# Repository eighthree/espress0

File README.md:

# espress0 prototype board
A Trinket m0 with SPI Flash + charge circuit 

# build one
https://oshpark.com

# license
Open Source
Creative Commons Attribution, Share-Alike license, check license.txt for more information. Derivative of "Trinket M0" (https://www.adafruit.com/product/3500)

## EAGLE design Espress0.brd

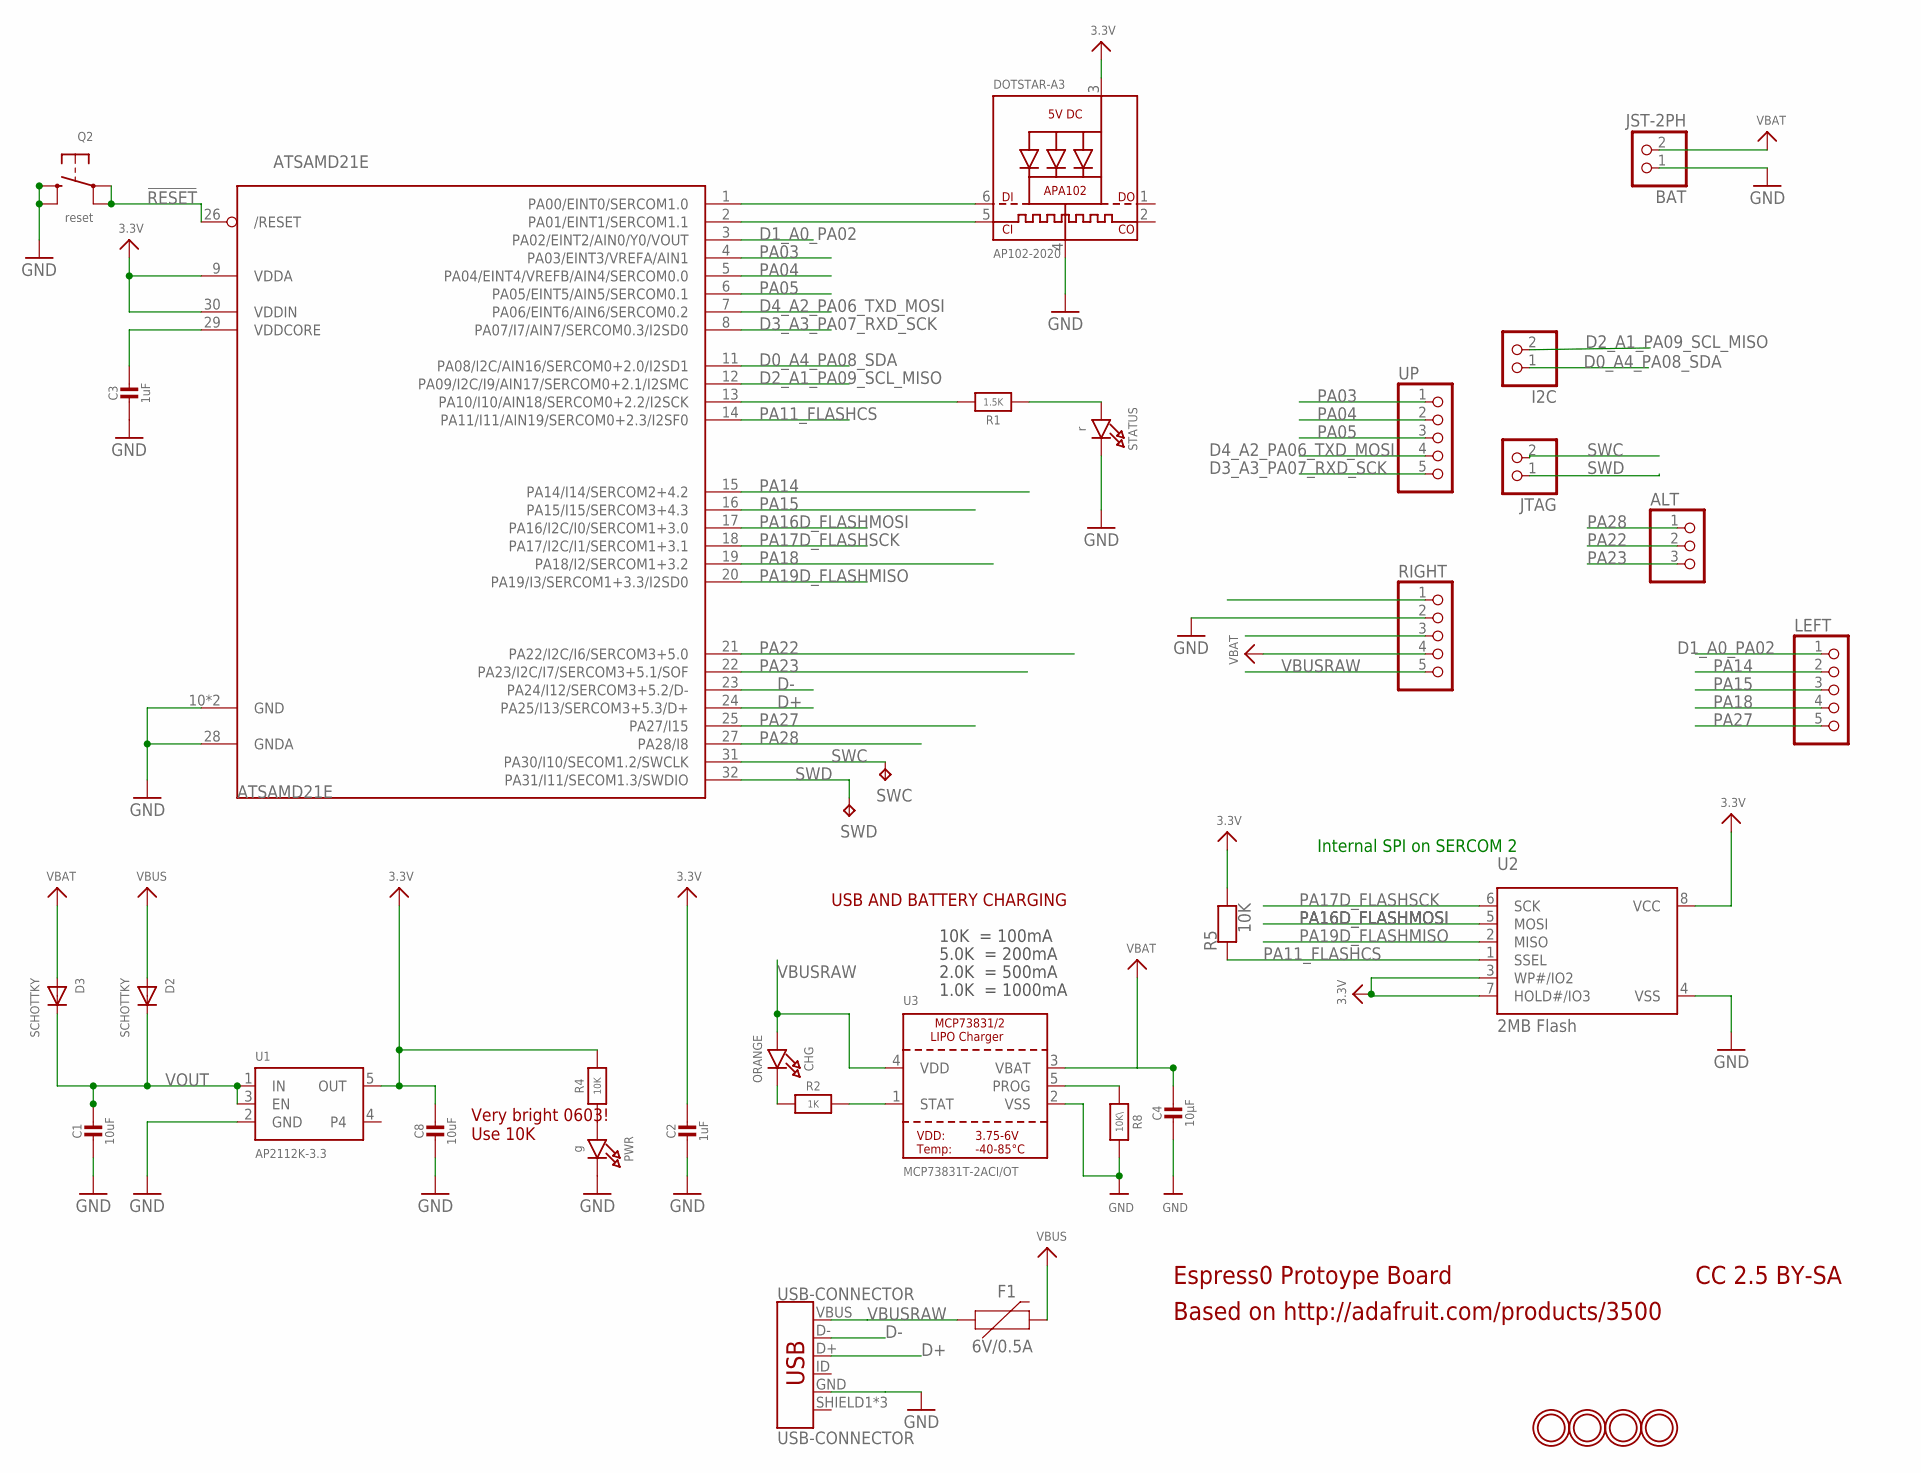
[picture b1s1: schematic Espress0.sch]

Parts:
ALT: PINHD-1X3CB; 1X03-CLEANBIG
ATSAMD21E: ATSAMD21E; QFN32_5MM
BAT: JST-2PH; JSTPH2
C1, C8: 10uF; 0805-NO
C2, C3: 1uF; 0603-NO
C4: 10µF; 0805-NO
CHG: ORANGE; CHIPLED_0805_NOOUTLINE
D2, D3: SCHOTTKY; SOD-123FL
DOTSTAR-A3: AP102-2020; APA102_2020
F1: 6V/0.5A; 1206
I2C: HEADER-1X2ROUND; 1X02_ROUND
JTAG: HEADER-1X2ROUND; 1X02_ROUND
LEFT: HEADER-1X576MIL; 1X05_ROUND_76
PWR: g; CHIPLED_0603_NOOUTLINE
Q2: reset; BTN_KMR2_4.6X2.8
R1: 1.5K; 0603-NO
R2: 1K; 0603-NO
R4, R5: 10K; 0603-NO
R8: 10K\; 0603-NO
RIGHT: HEADER-1X576MIL; 1X05_ROUND_76
STATUS: r; CHIPLED_0603_NOOUTLINE
SWC: TPB1,27; B1,27
SWD: TPB1,27; B1,27
U1: AP2112K-3.3; SOT23-5
U2: 2MB Flash; SOIC8_208MIL
U3: MCP73831T-2ACI/OT; SOT23-5
U$8, U$9, U$13, U$14: MOUNTINGHOLE2.0; MOUNTINGHOLE_2.0_PLATED
UP: HEADER-1X576MIL; 1X05_ROUND_76
USB-CONNECTOR: USB-CONNECTOR; USB-B-MICRO-SMD

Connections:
3.3V: ATSAMD21E.9 (VDDA), ATSAMD21E.30 (VDDIN), C2.1, C8.1, DOTSTAR-A3.3 (VDD), R4.2, R5.2, RIGHT.3, U1.5 (OUT), U2.3 (WP#/IO2), U2.7 (HOLD#/IO3), U2.8 (VCC)
!RESET: ATSAMD21E.26 (/RESET), Q2.A, Q2.A' (P1), RIGHT.1
A3: ATSAMD21E.1 (PA00/EINT0/SERCOM1.0), DOTSTAR-A3.6 (DI)
D0_A4_PA08_SDA: ATSAMD21E.11 (PA08/I2C/AIN16/SERCOM0+2.0/I2SD1), I2C.1
D1_A0_PA02: ATSAMD21E.3 (PA02/EINT2/AIN0/Y0/VOUT), LEFT.1
D2_A1_PA09_SCL_MISO: ATSAMD21E.12 (PA09/I2C/I9/AIN17/SERCOM0+2.1/I2SMC), I2C.2
D3_A3_PA07_RXD_SCK: ATSAMD21E.8 (PA07/I7/AIN7/SERCOM0.3/I2SD0), UP.5
D4_A2_PA06_TXD_MOSI: ATSAMD21E.7 (PA06/EINT6/AIN6/SERCOM0.2), UP.4
D+: ATSAMD21E.24 (PA25/I13/SERCOM3+5.3/D+), USB-CONNECTOR.D+
D-: ATSAMD21E.23 (PA24/I12/SERCOM3+5.2/D-), USB-CONNECTOR.D-
GND: ATSAMD21E.10 (GND), ATSAMD21E.28 (GNDA), ATSAMD21E.33 (GND), BAT.1, C1.2, C2.2, C3.2, C4.2, C8.2, DOTSTAR-A3.4 (GND), PWR.C, Q2.B (S), Q2.B' (S1), R8.2, RIGHT.2, STATUS.C, U1.2 (GND), U2.4 (VSS), U3.2 (VSS), USB-CONNECTOR.GND
unnamed: R1.1, STATUS.A
unnamed: ATSAMD21E.13 (PA10/I10/AIN18/SERCOM0+2.2/I2SCK), R1.2
unnamed: PWR.A, R4.1
unnamed: ATSAMD21E.2 (PA01/EINT1/SERCOM1.1), DOTSTAR-A3.5 (CKI)
unnamed: CHG.C, R2.1
unnamed: R2.2, U3.1 (STAT)
unnamed: R8.1, U3.5 (PROG)
PA03: ATSAMD21E.4 (PA03/EINT3/VREFA/AIN1), UP.1
PA04: ATSAMD21E.5 (PA04/EINT4/VREFB/AIN4/SERCOM0.0), UP.2
PA05: ATSAMD21E.6 (PA05/EINT5/AIN5/SERCOM0.1), UP.3
PA11_FLASHCS: ATSAMD21E.14 (PA11/I11/AIN19/SERCOM0+2.3/I2SF0), R5.1, U2.1 (SSEL)
PA14: ATSAMD21E.15 (PA14/I14/SERCOM2+4.2), LEFT.2
PA15: ATSAMD21E.16 (PA15/I15/SERCOM3+4.3), LEFT.3
PA16D_FLASHMOSI: ATSAMD21E.17 (PA16/I2C/I0/SERCOM1+3.0), U2.5 (MOSI)
PA17D_FLASHSCK: ATSAMD21E.18 (PA17/I2C/I1/SERCOM1+3.1), U2.6 (SCK)
PA18: ATSAMD21E.19 (PA18/I2/SERCOM1+3.2), LEFT.4
PA19D_FLASHMISO: ATSAMD21E.20 (PA19/I3/SERCOM1+3.3/I2SD0), U2.2 (MISO)
PA22: ALT.2, ATSAMD21E.21 (PA22/I2C/I6/SERCOM3+5.0)
PA23: ALT.3, ATSAMD21E.22 (PA23/I2C/I7/SERCOM3+5.1/SOF)
PA27: ATSAMD21E.25 (PA27/I15), LEFT.5
PA28: ALT.1, ATSAMD21E.27 (PA28/I8)
SWC: ATSAMD21E.31 (PA30/I10/SECOM1.2/SWCLK), JTAG.2, SWC.TP
SWD: ATSAMD21E.32 (PA31/I11/SECOM1.3/SWDIO), JTAG.1, SWD.TP
VBAT: BAT.2, C4.1, D3.A, RIGHT.4, U3.3 (VBAT)
VBUS: D2.A, F1.2
VBUSRAW: CHG.A, F1.1, RIGHT.5, U3.4 (VDD), USB-CONNECTOR.VBUS
VDDCORE: ATSAMD21E.29 (VDDCORE), C3.1
VOUT: C1.1, D2.C, D3.C, U1.1 (IN), U1.3 (EN)

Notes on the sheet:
Espress0 Protoype Board
Based on http://adafruit.com/products/3500
CC 2.5 BY-SA
Very bright 0603! Use 10K
Internal SPI on SERCOM 2
10K = 100mA
5.0K = 200mA
2.0K = 500mA
1.0K = 1000mA
USB AND BATTERY CHARGING

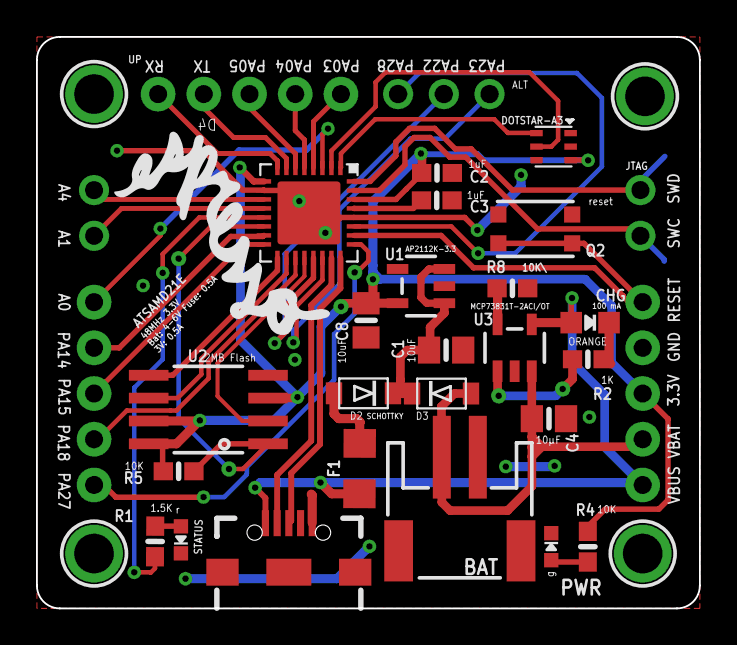
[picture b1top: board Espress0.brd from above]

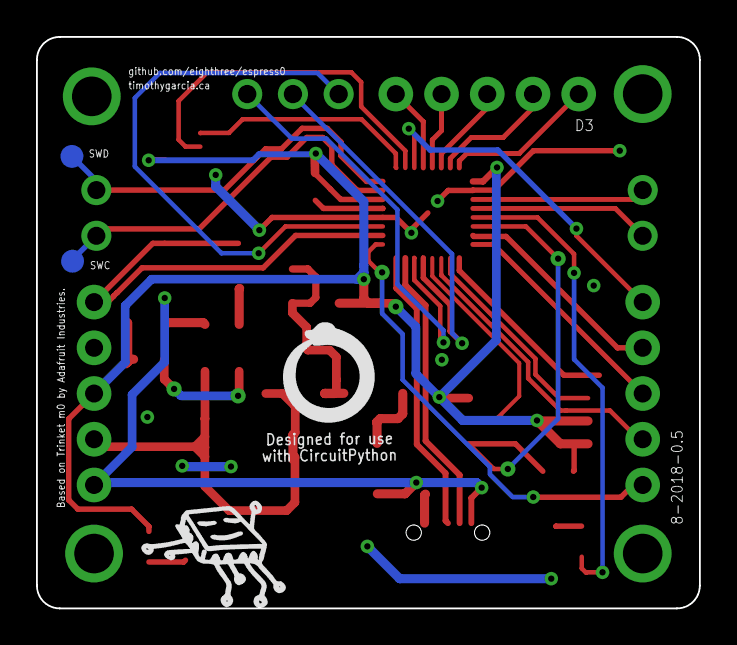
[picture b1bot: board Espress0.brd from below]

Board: 2 copper layers, 36.8 x 31.8 mm, 36 parts (2 on the bottom side), 39 nets.

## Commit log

2018-04-10 v0.3
    * Layout adjusted and schematic updated, pin header arrangement no longer matches 1:1 with a Trinket m0 board
    * Trace diameter for power lines adjusted for 20mm, data for 15mm
    * Removed "antennas", trapped copper that is grounded
    * Issues re: "Crosstalk" lines were adjusted to have more space and or GND between lines.
2018-04-10 Backlink to CADLAB.io has been added.
2018-04-10 Add files via upload
    Stray trace removed
2018-04-10 Add files via upload
    Removed a wiggle
2018-04-10 Add files via upload
    * Adjusted traces on VBAT, pa04, SDA, 3.3V lines on SPI flash and CS pin remap USB GND
2018-04-10 Add files via upload
    * Removed sharp & incorrect angles
    * CS Select pin fix
2018-04-10 Add files via upload
    * Fix on a data line
2018-04-10 Add files via upload
    * Via conflict with 3V rail
2018-04-10 Add files via upload
    * Fix micro USB grounding plane
2018-04-10 Add files via upload
    * SPI flash trace updates
2018-04-10 Add files via upload
    * Silkscreen updated
2018-04-10 Add files via upload
    * fix misplaced via, silkscreen updates
2018-04-10 v0.3
    Production
2018-04-10 Board preview
2018-04-27 CP2.2 Firmware for r0.3
    Circuitpython 2.2.4-5
    For use with Winbond WS25Q16FV
2018-04-27 CP2.2 Firmware for r0.1
    Circuitpython 2.2.4-5
    Can be used with r0.3 but uses a different flash chip
    For use with Winbond WS25Q32BV
2018-08-02 v0.5
    * New form factor, pins broken out as pads
    * 6V/500mA polyfuse between USB 5V+ and the voltage regulator
2018-08-03 Silkscreen
2018-08-03 Silkscreen thumbnail update
2018-08-04 Back silkscreen
2018-08-28 Create LICENSE
2018-10-09 Update LICENSE

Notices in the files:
parts and their libraries:
microbuilder: This work is placed in the public domain, and may be freely used for commercial and non-commercial work with the following conditions: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
SparkFun-Connectors: Licensing: Creative Commons ShareAlike 4.0 International - https://creativecommons.org/licenses/by-sa/4.0
